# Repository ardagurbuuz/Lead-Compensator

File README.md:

# Analog Lead Compensator Controller (Plant + Compensator)

This repository documents an end-to-end control + hardware workflow: **designing a lead compensator**, validating it at **model-level (MATLAB/Simulink)** and **circuit-level (SPICE tools)**, and implementing it as an **op-amp analog controller** on a **KiCad PCB**.

A benchmark plant model is used as the baseline system:

$$
G(s)=\frac{2}{s(s+1)}
$$

---

## System overview (what is being built)
The project compares two closed-loop configurations under the same input:

1. **Uncompensated loop:** plant-only closed-loop response  
2. **Compensated loop:** plant + lead compensator closed-loop response  

This block-level structure is implemented and cross-validated across tools:

---

## What this project is (and why it matters)
A **lead compensator** adds **phase lead** in a chosen frequency range. Practically, it helps achieve:
- **faster transient response** (shorter settling time),
- **reduced overshoot**,
- improved stability margins when the baseline plant dynamics are “too slow” or “too oscillatory”.

### Why this plant?
The plant

`G(s) = 2 / (s(s+1))`

was chosen deliberately because it is a **clean benchmark** that exposes the core trade-offs a lead compensator is meant to address:
- The `1/s` term introduces an **integrator**, which is a common structure when the system output represents an accumulated quantity (position/angle/level).
- The `1/(s+1)` term adds a **dominant first-order lag**, a very typical dynamic limitation in real systems.
- Together, this plant is simple enough to analyze clearly, yet rich enough to show meaningful improvements in transient behavior when compensation is applied.

In short: it’s an intentional baseline that makes controller impact measurable and transferable.

---

## Design goals
The project is built around a single, clear comparison:
- **Uncompensated (plant-only)** response
vs.
- **Compensated (plant + lead compensator)** response

with the intent to improve transient performance (reduced overshoot, faster settling) while keeping the design implementable in analog hardware.

---

## Control design method (Root Locus)
The compensator was selected using **Root Locus–based design**, specifically:
- **Dominant pole targeting:** choose desired dominant closed-loop pole locations that meet transient expectations (overshoot/settling trade-off).
- **Angle condition:** determine where a compensator zero/pole should be placed so the desired pole location satisfies the Root Locus angle requirement.
- **Magnitude condition:** compute the required gain so the point lies on the locus.

This approach links performance objectives directly to pole locations and results in a compensator that is both analyzable and implementable.

---

## Verification workflow (MATLAB → Simulink → SPICE tools)
This project intentionally uses multiple tools because each one answers a different question. Using only one would leave blind spots.

### 1) MATLAB (calculation sanity-check)
MATLAB is used to verify the math: pole/zero placement logic, gain consistency, and quick numeric checks. This prevents “it looks right” errors before simulation.

### 2) Simulink (system-level behavior)
Simulink is used to observe **signals and step responses** in a clean block-diagram environment and to compare compensated vs. uncompensated outputs under the same stimulus.

### 3) LTspice (ideal circuit-level cross-check)
LTspice is used to rebuild the control structure as **ideal analog circuits**, for two reasons:
- It verifies the design **at circuit level** (not only transfer-function level).
- It enables quick iteration and clean A/B comparison of plant-only vs. compensated behavior.

### 4) Proteus (practical pre-PCB simulation + switching)
Proteus is used as the “last realism check” before committing to PCB:
- It supports a **switch-based** workflow: using a DPDT switch model to **toggle between plant-only and compensated paths**, enabling direct comparison with the same source/instrumentation.
- It is also convenient for validating the integrated circuit behavior and wiring logic in a more “lab-like” simulation setup.

In short:
- **LTspice (SPICE tool)** = ideal, controlled circuit verification and fast iteration  
- **Proteus (SPICE tool)** = integrated validation with switching and final pre-PCB confidence

---

## Hardware implementation (Analog + PCB)
After validating behavior in simulation, the controller is implemented using **op-amp analog circuitry** and captured in KiCad as:
- schematic,
- PCB layout and routing,
- manufacturing-ready board representation.

A key constraint throughout the hardware step is **real-world component availability**:
- Some ideal resistor values from initial calculations are not standard off-the-shelf values.
- Where needed, values are realized using **series/parallel combinations** (documented/verified at simulation stage before PCB finalization).

> Fabrication note: The current PCB is a **2-layer** design. If single-sided fabrication is required, it will generally need rerouting and/or jumpers.

---

## Reproducibility (how to run / view everything)
This repo is structured so each stage can be opened independently.

### MATLAB / Simulink
Folder: `matlab-simulink/`
- `lead_compensator.m` → calculation/verification script
- `plant_comp.slx` → compensated system model
- `uncomp_step_response.slx` → baseline (plant-only) response model

Open in MATLAB/Simulink and run the script/models to reproduce the response comparison.

### LTspice
Folder: `ltspice/`
- `lead-compensator.asc` → circuit file

Open in LTspice and run the transient simulation to inspect waveforms.

### Proteus
Folder: `proteus/`
- `lead-compensator.pdsprj` → project file (includes switch-based comparison setup)

Open in Proteus, run simulation, and toggle the switch to compare modes.

### KiCad
Folder: `kicad/`
- `lead-compensator.kicad_sch` → schematic
- `lead-compensator.kicad_pcb` → PCB layout
- `lead-compensator.kicad_pro` → project settings

Open the `.kicad_pro` project file in KiCad, then inspect schematic/PCB.

---

## Repository structure
- `docs/images/` → curated images used in README
- `kicad/` → KiCad schematic + PCB
- `matlab-simulink/` → MATLAB + Simulink models
- `ltspice/` → LTspice circuit (SPICE tool)
- `proteus/` → Proteus project (SPICE tool)

---

## Tools
**MATLAB, Simulink, LTspice (SPICE tool), Proteus (SPICE tool), KiCad**

---

## Keywords (for recruiters and technical readers)
Root Locus, dominant poles, angle condition, magnitude condition, lead compensator, transient response, overshoot, settling time, circuit-level validation, op-amp analog implementation, PCB design, DRC-clean layout, end-to-end engineering workflow.

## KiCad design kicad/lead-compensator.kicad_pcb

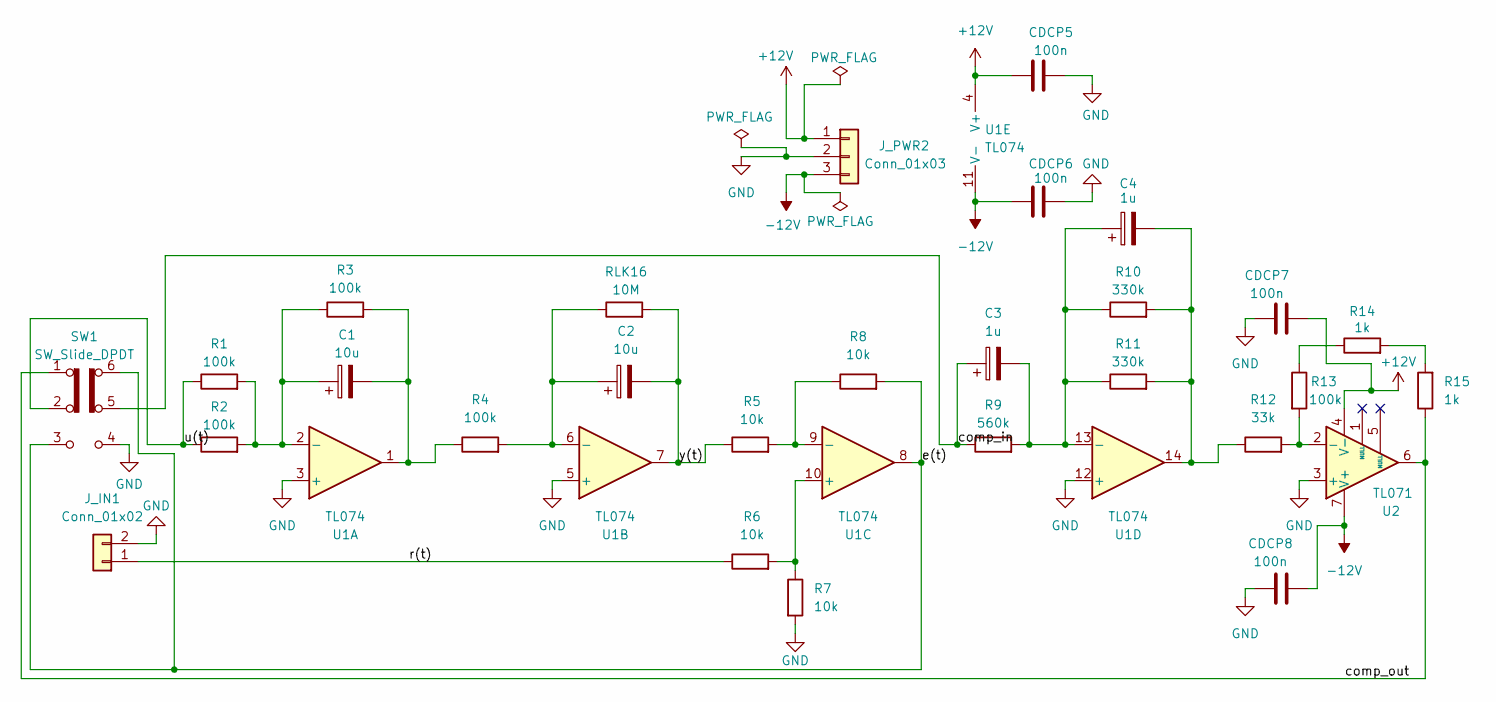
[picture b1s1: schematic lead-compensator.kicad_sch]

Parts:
C1, C2: 10u; C_Radial_D5.0mm_H11.0mm_P2.00mm
C3, C4: 1u; C_Radial_D5.0mm_H11.0mm_P2.00mm
CDCP5, CDCP6, CDCP7, CDCP8: 100n; C_Rect_L4.6mm_W3.8mm_P2.50mm_MKS02_FKP02
J_IN1: Conn_01x02; TerminalBlock_Degson_DG250-3.5-02P_1x02_P3.50mm_45Degree
J_PWR2: Conn_01x03; TerminalBlock_Degson_DG250-3.5-03P_1x03_P3.50mm_45Degree
R1, R2, R3, R4, R13: 100k; R_Axial_DIN0207_L6.3mm_D2.5mm_P7.62mm_Horizontal
R5, R6, R7, R8: 10k; R_Axial_DIN0204_L3.6mm_D1.6mm_P5.08mm_Horizontal
R9: 560k; R_Axial_DIN0207_L6.3mm_D2.5mm_P7.62mm_Horizontal
R10, R11: 330k; R_Axial_DIN0414_L11.9mm_D4.5mm_P15.24mm_Horizontal
R12: 33k; R_Axial_DIN0207_L6.3mm_D2.5mm_P7.62mm_Horizontal
R14, R15: 1k; R_Axial_DIN0204_L3.6mm_D1.6mm_P5.08mm_Horizontal
RLK16: 10M; R_Axial_DIN0309_L9.0mm_D3.2mm_P12.70mm_Horizontal
SW1: SW_Slide_DPDT; SW_CK_JS202011AQN_DPDT_Angled
U1: TL074; DIP-14_W7.62mm
U2: TL071; DIP-8_W7.62mm

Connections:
+12V: CDCP5.1, CDCP7.2, J_PWR2.1, U1.4 (V+), U2.4 (V-)
-12V: CDCP6.1, CDCP8.2, J_PWR2.3, U1.11 (V-), U2.7 (V+)
/comp_in: C3.1, R9.1, SW1.5 (B)
/comp_out: R15.1, SW1.1 (A), U2.6
/e(t): R8.2, SW1.3 (C), SW1.6 (C), U1.8
/r(t): J_IN1.1, R6.1
/u(t): R1.1, R2.1, SW1.2 (B)
/y(t): C2.2, R5.1, RLK16.2, U1.7
GND: CDCP5.2, CDCP6.2, CDCP7.1, CDCP8.1, J_IN1.2, J_PWR2.2, R7.2, SW1.4 (A), U1.3 (+), U1.5 (+), U1.12 (+), U2.3 (+)
unnamed: C1.2, R3.2, R4.1, U1.1
unnamed: C4.2, R10.2, R11.2, R12.1, U1.14
unnamed: R13.1, R14.1
unnamed: R14.2, R15.2
unnamed: C1.1, R1.2, R2.2, R3.1, U1.2 (-)
unnamed: C2.1, R4.2, RLK16.1, U1.6 (-)
unnamed: R6.2, R7.1, U1.10 (+)
unnamed: R5.2, R8.1, U1.9 (-)
unnamed: C3.2, C4.1, R9.2, R10.1, R11.1, U1.13 (-)
unnamed: R12.2, R13.2, U2.2 (-)

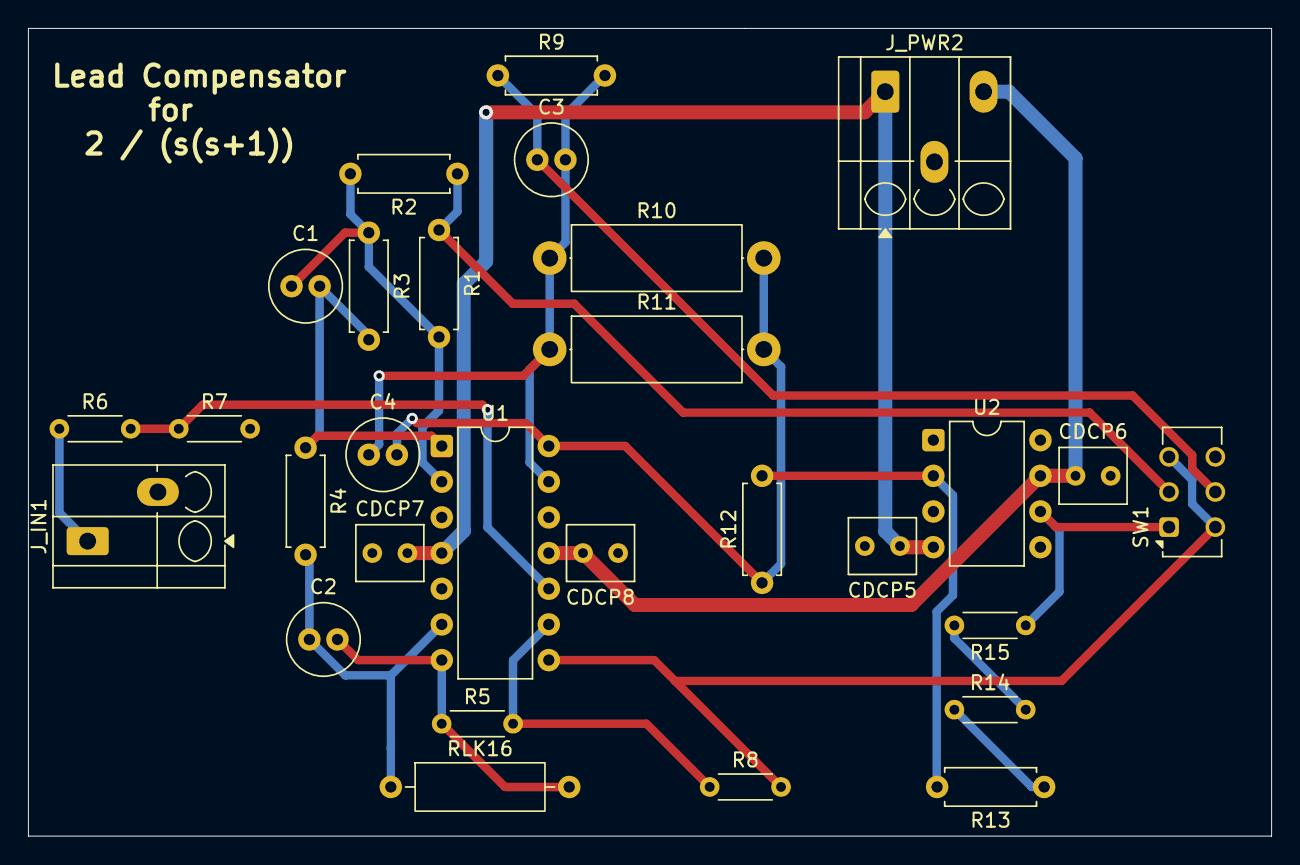
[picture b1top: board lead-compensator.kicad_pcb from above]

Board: 2 copper layers, 88.5 x 57.5 mm, 29 parts (0 on the bottom side), 19 nets.

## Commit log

2026-02-17 Add project README
2026-02-17 Rename KiCad project files
